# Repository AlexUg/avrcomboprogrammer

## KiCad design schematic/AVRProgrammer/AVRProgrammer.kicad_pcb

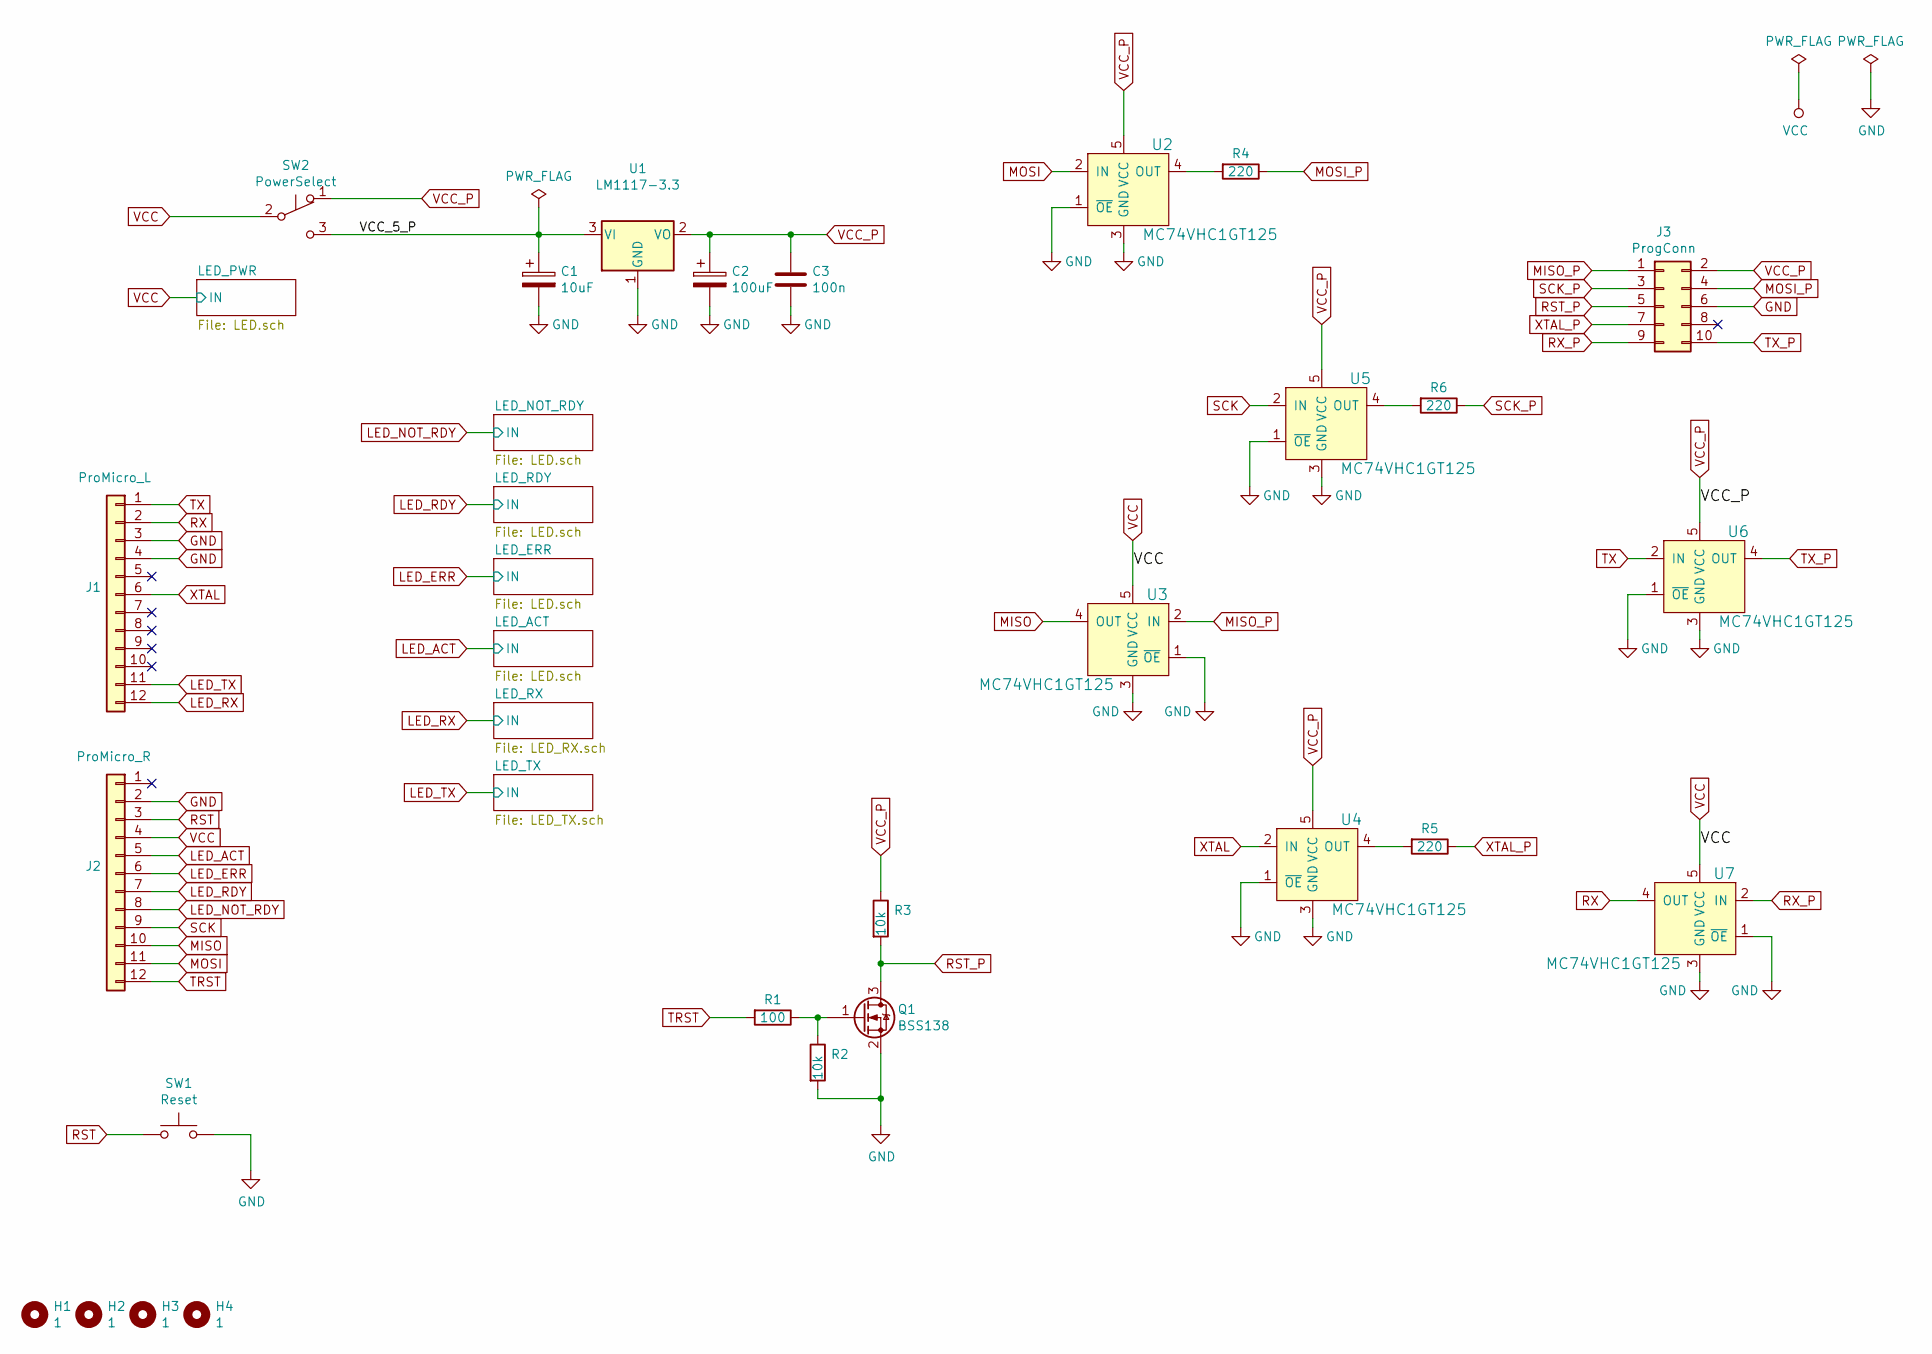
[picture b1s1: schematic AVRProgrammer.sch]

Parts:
C1: 10uF; CP_Elec_5x5.9
C2: 100uF; CP_Elec_5x5.9
C3: 100n; C_0805_2012Metric
H1, H2, H3, H4: 1; MountingHole_2.7mm_M2.5
J1: ProMicro_L; PinSocket_1x12_P2.54mm_Vertical
J2: ProMicro_R; PinSocket_1x12_P2.54mm_Vertical
J3: ProgConn; IDC-Header_2x05_P2.54mm_Horizontal
Q1: BSS138; SOT-23
R1: 100; R_0805_2012Metric
R2, R3: 10k; R_0805_2012Metric
R4, R5, R6: 220; R_0805_2012Metric
SW1: Reset; Button_6
SW2: PowerSelect; PD9-2
U1: LM1117-3.3; SOT-223-3_TabPin2
U2, U3, U4, U5, U6, U7: MC74VHC1GT125; SOT-23-5

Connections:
/VCC_5_P: C1.1, SW2.3 (C), U1.3 (VI)
GND: C1.2, C2.2, C3.2, J1.3, J1.4, J2.2, J3.6, Q1.2 (S), R2.2, SW1.2, U1.1 (GND), U2.1 (~OE), U2.3 (GND), U3.1 (~OE), U3.3 (GND), U4.1 (~OE), U4.3 (GND), U5.1 (~OE), U5.3 (GND), U6.1 (~OE), U6.3 (GND), U7.1 (~OE), U7.3 (GND); also elsewhere on the board
LED_ACT: J2.5; also elsewhere on the board
LED_ERR: J2.6; also elsewhere on the board
LED_NOT_RDY: J2.8; also elsewhere on the board
LED_RDY: J2.7; also elsewhere on the board
LED_RX: J1.12; also elsewhere on the board
LED_TX: J1.11; also elsewhere on the board
MISO: J2.10, U3.4 (OUT)
MISO_P: J3.1, U3.2 (IN)
MOSI: J2.11, U2.2 (IN)
MOSI_P: J3.4, R4.1
unnamed: Q1.1 (G), R1.1, R2.1
unnamed: R4.2, U2.4 (OUT)
unnamed: R5.2, U4.4 (OUT)
unnamed: R6.2, U5.4 (OUT)
RST: J2.3, SW1.1
RST_P: J3.5, Q1.3 (D), R3.2
RX: J1.2, U7.4 (OUT)
RX_P: J3.9, U7.2 (IN)
SCK: J2.9, U5.2 (IN)
SCK_P: J3.3, R6.1
TRST: J2.12, R1.2
TX: J1.1, U6.2 (IN)
TX_P: J3.10, U6.4 (OUT)
VCC: J2.4, SW2.2 (B), U3.5 (VCC), U7.5 (VCC); also elsewhere on the board
VCC_P: C2.1, C3.1, J3.2, R3.1, SW2.1 (A), U1.2 (VO), U2.5 (VCC), U4.5 (VCC), U5.5 (VCC), U6.5 (VCC)
XTAL: J1.6, U4.2 (IN)
XTAL_P: J3.7, R5.1

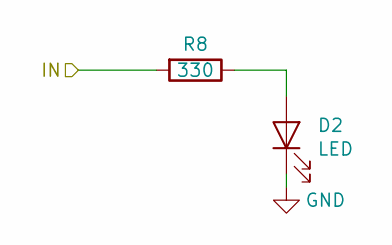
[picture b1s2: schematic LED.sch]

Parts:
D1: LED; LED_D3.0mm
R7: 330; R_0805_2012Metric

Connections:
GND: D1.1 (K); also elsewhere on the board
LED_NOT_RDY: R7.2; also elsewhere on the board
unnamed: D1.2 (A), R7.1

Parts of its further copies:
D2, D3, D4, D5, D6, D7: LED; LED_D3.0mm
R8, R9, R10, R11, R12, R13: 330; R_0805_2012Metric

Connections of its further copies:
GND: D2.1 (K), D3.1 (K), D4.1 (K), D5.1 (K), D6.1 (K), D7.1 (K); also elsewhere on the board
LED_ACT: R10.2; also elsewhere on the board
LED_ERR: R9.2; also elsewhere on the board
LED_RDY: R8.2; also elsewhere on the board
LED_RX: R11.2; also elsewhere on the board
LED_TX: R12.2; also elsewhere on the board
unnamed: D2.2 (A), R8.1
unnamed: D3.2 (A), R9.1
unnamed: D4.2 (A), R10.1
unnamed: D5.2 (A), R11.1
unnamed: D6.2 (A), R12.1
unnamed: D7.2 (A), R13.1
VCC: R13.2; also elsewhere on the board

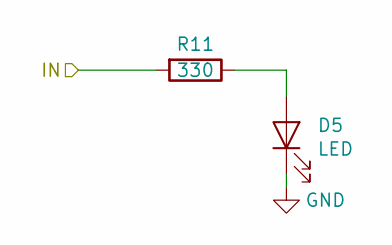
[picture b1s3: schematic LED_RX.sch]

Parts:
D1: LED; LED_D3.0mm_Horizontal_O6.35mm_Z6.0mm
R7: 330; R_0805_2012Metric

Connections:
GND: D1.1 (K); also elsewhere on the board
LED_NOT_RDY: R7.2; also elsewhere on the board
unnamed: D1.2 (A), R7.1

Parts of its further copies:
D2, D3, D4, D5, D6, D7: LED; LED_D3.0mm_Horizontal_O6.35mm_Z6.0mm
R8, R9, R10, R11, R12, R13: 330; R_0805_2012Metric

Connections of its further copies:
GND: D2.1 (K), D3.1 (K), D4.1 (K), D5.1 (K), D6.1 (K), D7.1 (K); also elsewhere on the board
LED_ACT: R10.2; also elsewhere on the board
LED_ERR: R9.2; also elsewhere on the board
LED_RDY: R8.2; also elsewhere on the board
LED_RX: R11.2; also elsewhere on the board
LED_TX: R12.2; also elsewhere on the board
unnamed: D2.2 (A), R8.1
unnamed: D3.2 (A), R9.1
unnamed: D4.2 (A), R10.1
unnamed: D5.2 (A), R11.1
unnamed: D6.2 (A), R12.1
unnamed: D7.2 (A), R13.1
VCC: R13.2; also elsewhere on the board

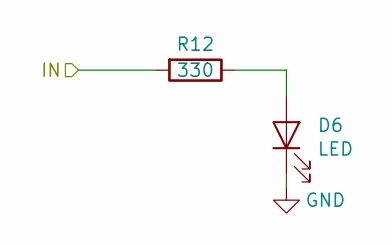
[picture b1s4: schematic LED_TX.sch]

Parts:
D1: LED; LED_D3.0mm_Horizontal_O1.27mm_Z2.0mm
R7: 330; R_0805_2012Metric

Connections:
GND: D1.1 (K); also elsewhere on the board
LED_NOT_RDY: R7.2; also elsewhere on the board
unnamed: D1.2 (A), R7.1

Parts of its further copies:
D2, D3, D4, D5, D6, D7: LED; LED_D3.0mm_Horizontal_O1.27mm_Z2.0mm
R8, R9, R10, R11, R12, R13: 330; R_0805_2012Metric

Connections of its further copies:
GND: D2.1 (K), D3.1 (K), D4.1 (K), D5.1 (K), D6.1 (K), D7.1 (K); also elsewhere on the board
LED_ACT: R10.2; also elsewhere on the board
LED_ERR: R9.2; also elsewhere on the board
LED_RDY: R8.2; also elsewhere on the board
LED_RX: R11.2; also elsewhere on the board
LED_TX: R12.2; also elsewhere on the board
unnamed: D2.2 (A), R8.1
unnamed: D3.2 (A), R9.1
unnamed: D4.2 (A), R10.1
unnamed: D5.2 (A), R11.1
unnamed: D6.2 (A), R12.1
unnamed: D7.2 (A), R13.1
VCC: R13.2; also elsewhere on the board

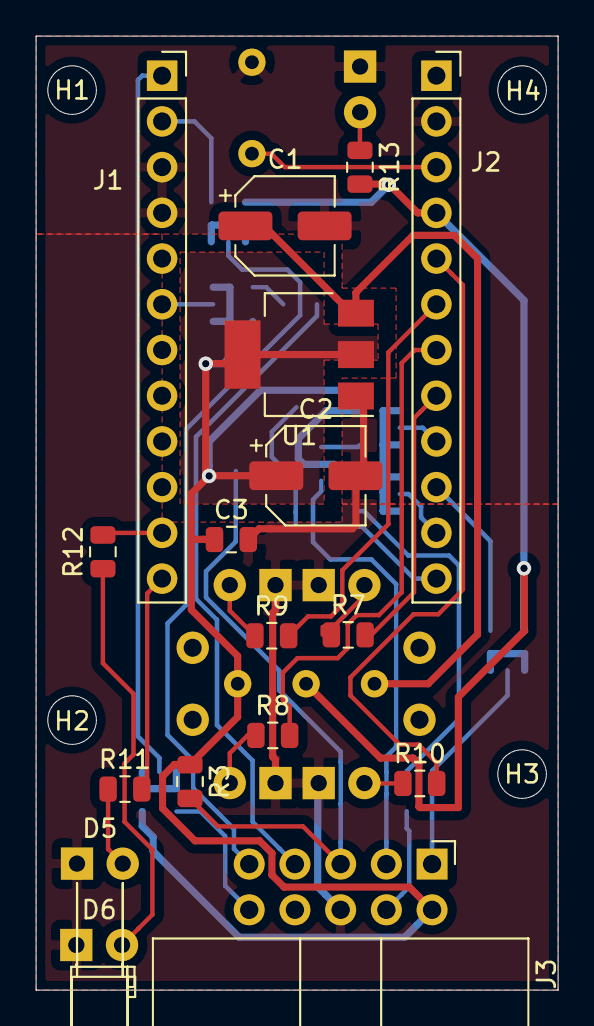
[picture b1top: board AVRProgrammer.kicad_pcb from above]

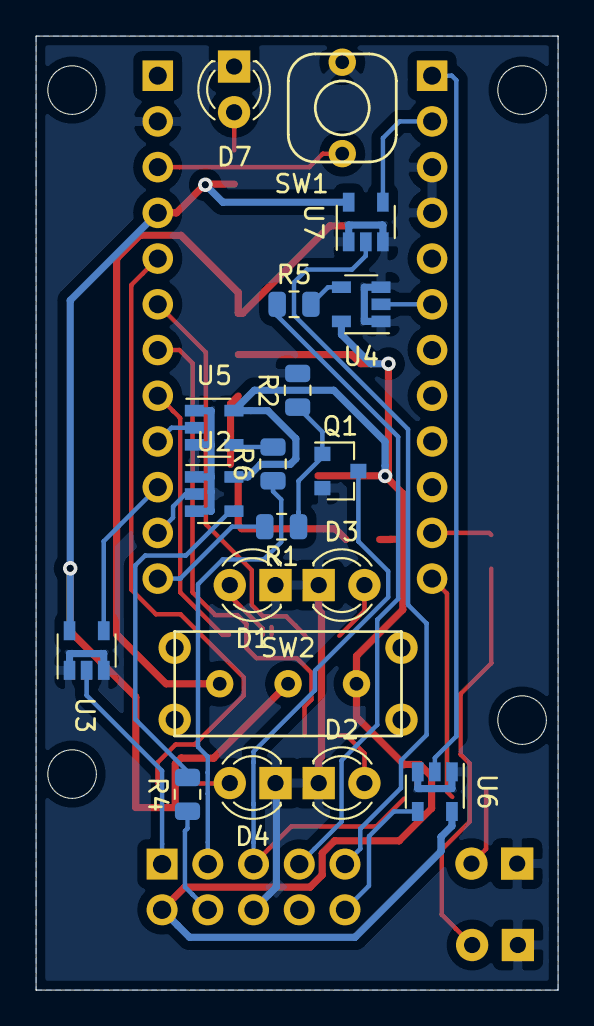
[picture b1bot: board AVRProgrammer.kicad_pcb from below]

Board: 2 copper layers, 29.0 x 53.0 mm, 40 parts (19 on the bottom side), 36 nets.

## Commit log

2019-03-31 Schematic first version
2019-03-31 Add warning to PCB. Add .gitignore
2019-04-14 3dmodels for PCB components was added
2019-04-14 3dmodels for programmer case were added
2019-04-14 Initial implementation of software for programmer
2019-04-14 Timer3 is used for timeouts for ISP and Serial. Timer0 is used for RescueCLK (4MHz).
2019-04-15 DTR (Reset) line was enabled
2019-04-15 Update programmer case. Remove 3dmodel *.obj files
2021-03-06 Mistakenly added files were removed
